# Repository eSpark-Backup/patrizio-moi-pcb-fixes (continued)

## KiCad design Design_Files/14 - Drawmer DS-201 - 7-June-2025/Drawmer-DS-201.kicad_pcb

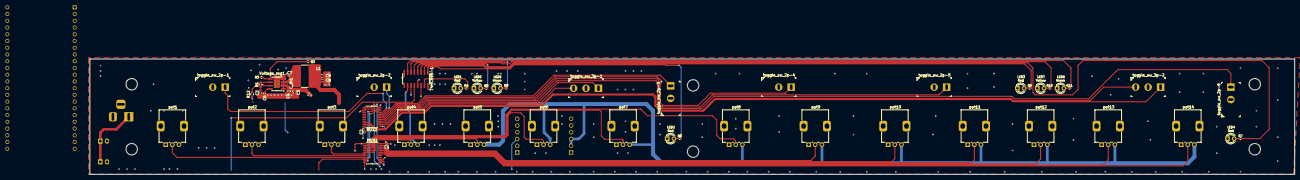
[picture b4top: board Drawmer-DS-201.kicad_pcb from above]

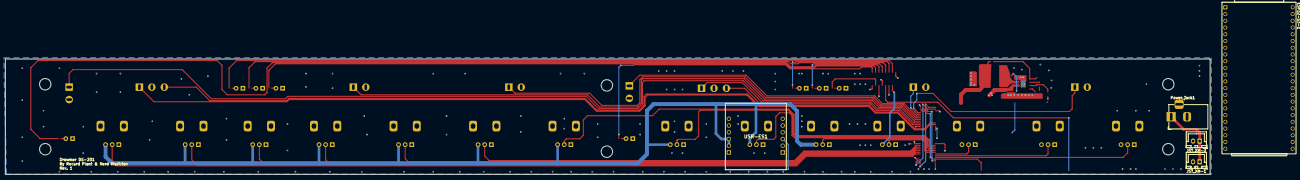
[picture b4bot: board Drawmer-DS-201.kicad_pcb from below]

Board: 4 copper layers, 454.4 x 43.5 mm, 62 parts (5 on the bottom side), 65 nets.

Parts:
74HC595-1: 74HC595; SOIC-16_3.9x9.9mm_P1.27mm
C1, C2: 0.1uF; C_0402_1005Metric
C3: 3.3 nF; C_0603_1608Metric
C4, C6, C7: 0.1 µF; C_0402_1005Metric
C5, C8, C9: 22uF; C_0603_1608Metric
C_IN1: 4.7 µF; C_0402_1005Metric
ESP32-S3-1: ESP32-S3-DevKitC; ESP32-S3-DEVKITC-1-N8R2-2
JST_XH-1, JST_XH-2: JST_XH_2_Pin; JST_XH_B2B-XH-A_1x02_P2.50mm_Vertical
L1: 10µH; L_Bourns-SRN8040_8x8.15mm
LED1, LED2, LED3, LED4: Red; LED_D3.0mm_Clear-2
LED5, LED7: Yellow; LED_D3.0mm_Clear-2
LED6, LED8: Green; LED_D3.0mm_Clear-2
MUX1, MUX2: CD4067BMT/TR; TSSOP-24_4.4x7.8mm_P0.65mm
Power_jack1: Jack-DC; BarrelJack_Horizontal
R1: 6.8kΩ; R_0603_1608Metric
R2: 43 kΩ; R_0402_1005Metric
R3: 10 kΩ; R_0402_1005Metric
R4, R5, R6, R7, R8, R9, R10, R11: 330Ω; R_0402_1005Metric
R12: 100kΩ; R_0603_1608Metric
USR-ES1: USR-ES1; USRES1
Voltage_reg1: MP2307DN-LF-Z; SOIC-8-1EP_3.9x4.9mm_P1.27mm_EP2.29x3mm_ThermalVias
pot1, pot2, pot3, pot4, pot5, pot6, pot7, pot8, pot9, pot10, pot11, pot12, pot13, pot14: b10k; Potentiometer_Alps_RK09K_Single_Vertical
toggle_sw_2p-1, toggle_sw_2p-2, toggle_sw_2p-3, toggle_sw_2p-4, toggle_sw_2p-5, toggle_sw_2p-6: toggle_sw_2p; Toggle_Switch-2-pins
toggle_sw_3p-1, toggle_sw_3p-2: toggle_sw_3p; Toggle_Switch-3-pins

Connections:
3.3V: 74HC595-1.10 (~SRCLR), 74HC595-1.16 (VCC), C1.2, C2.2, ESP32-S3-1.1 (3V3), ESP32-S3-1.2 (3V3), MUX1.24 (VCC), MUX2.24 (VCC), USR-ES1.B2 (3V3_1), USR-ES1.B3 (3V3_2), pot1.3, pot2.3, pot3.3, pot4.3, pot5.3, pot6.3, pot7.3, pot8.3, pot9.3, pot10.3, pot11.3, pot12.3, pot13.3, pot14.3
/LEDs/LED_A_QA: 74HC595-1.15 (QA), R4.2
/LEDs/LED_A_QB: 74HC595-1.1 (QB), R5.2
/LEDs/LED_A_QC: 74HC595-1.2 (QC), R6.2
/LEDs/LED_A_QD: 74HC595-1.3 (QD), R7.2
/LEDs/LED_A_QE: 74HC595-1.4 (QE), R8.2
/LEDs/LED_A_QF: 74HC595-1.5 (QF), R10.2
/LEDs/LED_A_QG: 74HC595-1.6 (QG), R9.2
/LEDs/LED_A_QH: 74HC595-1.7 (QH), R11.2
BOOT: C7.2, Voltage_reg1.1 (BS)
CS: ESP32-S3-1.5 (GPIO5/ADC1_CH4), USR-ES1.A5 (CS)
EXT_12V: C4.1, C5.2, C_IN1.1, JST_XH-1.1, JST_XH-2.1, Power_jack1.1, R12.1, Voltage_reg1.2 (IN)
GND: 74HC595-1.8 (GND), 74HC595-1.13 (~OE), C1.1, C2.1, C3.2, C4.2, C5.1, C6.2, C8.2, C9.2, C_IN1.2, ESP32-S3-1.22 (GND), ESP32-S3-1.23 (GND), ESP32-S3-1.24 (GND), ESP32-S3-1.44 (GND), JST_XH-1.2, JST_XH-2.2, LED1.1 (K), LED2.1 (K), LED3.1 (K), LED4.1 (K), LED5.1 (K), LED6.1 (K), LED7.1 (K), LED8.1 (K), MUX1.12 (GND), MUX1.15 (~E), MUX2.12 (GND), MUX2.15 (~E), Power_jack1.2, R3.2, USR-ES1.A1 (GND_1), USR-ES1.A2 (GND_2), USR-ES1.B1 (GND_3), Voltage_reg1.4 (GND), Voltage_reg1.9 (EP), pot1.1, pot2.1, pot3.1, pot4.1, pot5.1, pot6.1, pot7.1, pot8.1, pot9.1, pot10.1, pot11.1, pot12.1, pot13.1, pot14.1, toggle_sw_2p-1.2 (B), toggle_sw_2p-2.2 (B), toggle_sw_2p-3.2 (B), toggle_sw_2p-4.2 (B), toggle_sw_2p-5.2 (B), toggle_sw_2p-6.2 (B), toggle_sw_3p-1.2 (B), toggle_sw_3p-2.2 (B)
I0: MUX1.9 (I0), pot1.2
I1: MUX1.8 (I1), pot2.2
I2: MUX1.7 (I2), pot3.2
I3: MUX1.6 (I3), pot4.2
I4: MUX1.5 (I4), pot5.2
I5: MUX1.4 (I5), pot6.2
I6: MUX1.3 (I6), pot7.2
I7: MUX1.2 (I7), pot8.2
I8: MUX1.23 (I8), pot9.2
I9: MUX1.22 (I9), pot10.2
I10: MUX1.21 (I10), pot11.2
I11: MUX1.20 (I11), pot12.2
I12: MUX1.19 (I12), pot13.2
I13: MUX1.18 (I13), pot14.2
INT: ESP32-S3-1.7 (GPIO7/ADC1_CH6), USR-ES1.A6 (INT)
J0: MUX2.9 (I0), toggle_sw_2p-1.1 (A)
J1: MUX2.8 (I1), toggle_sw_2p-2.1 (A)
J2: MUX2.7 (I2), toggle_sw_2p-3.1 (A)
J3: MUX2.6 (I3), toggle_sw_2p-4.1 (A)
J4: MUX2.5 (I4), toggle_sw_2p-5.1 (A)
J5: MUX2.4 (I5), toggle_sw_2p-6.1 (A)
J6: MUX2.3 (I6), toggle_sw_3p-1.1 (A)
J7: MUX2.2 (I7), toggle_sw_3p-1.3 (C)
J8: MUX2.23 (I8), toggle_sw_3p-2.1 (A)
J9: MUX2.22 (I9), toggle_sw_3p-2.3 (C)
MISO: ESP32-S3-1.33 (GPIO36), USR-ES1.B6 (MISO)
MOSI: ESP32-S3-1.32 (GPIO35), USR-ES1.A3 (MOSI)
unnamed: C3.1, R1.1
unnamed: LED1.2 (A), R4.1
unnamed: LED2.2 (A), R5.1
unnamed: LED3.2 (A), R6.1
unnamed: LED4.2 (A), R7.1
unnamed: LED5.2 (A), R8.1
unnamed: LED6.2 (A), R9.1
unnamed: LED7.2 (A), R10.1
unnamed: LED8.2 (A), R11.1
unnamed: R1.2, Voltage_reg1.6 (COMP)
unnamed: R12.2, Voltage_reg1.7 (EN)
unnamed: R2.2, R3.1, Voltage_reg1.5 (FB)
unnamed: C6.1, Voltage_reg1.8 (SS)
unnamed: C7.1, L1.1, Voltage_reg1.3 (SW)
RCLK_latch: 74HC595-1.12 (RCLK), ESP32-S3-1.40 (GPIO2/ADC1_CH1)
REG_5V: C8.1, C9.1, ESP32-S3-1.21 (5V), L1.2, R2.1
RST: ESP32-S3-1.35 (GPIO38), USR-ES1.B5 (RST)
S0: ESP32-S3-1.27 (GPIO21), MUX1.10 (S0), MUX2.10 (S0)
S1: ESP32-S3-1.34 (GPIO37), MUX1.11 (S1), MUX2.11 (S1)
S2: ESP32-S3-1.30 (GPIO45), MUX1.14 (S2), MUX2.14 (S2)
S3: ESP32-S3-1.28 (GPIO47), MUX1.13 (S3), MUX2.13 (S3)
SCLK: 74HC595-1.11 (SRCLK), ESP32-S3-1.11 (GPIO18/ADC2_CH7), USR-ES1.A4 (SCLK)
SER: 74HC595-1.14 (SER), ESP32-S3-1.4 (GPIO4/ADC1_CH3)
sig_1: ESP32-S3-1.41 (GPIO1/ADC1_CH0), MUX1.1 (COM)
sig_2: ESP32-S3-1.13 (GPIO3/ADC1_CH2), MUX2.1 (COM)
